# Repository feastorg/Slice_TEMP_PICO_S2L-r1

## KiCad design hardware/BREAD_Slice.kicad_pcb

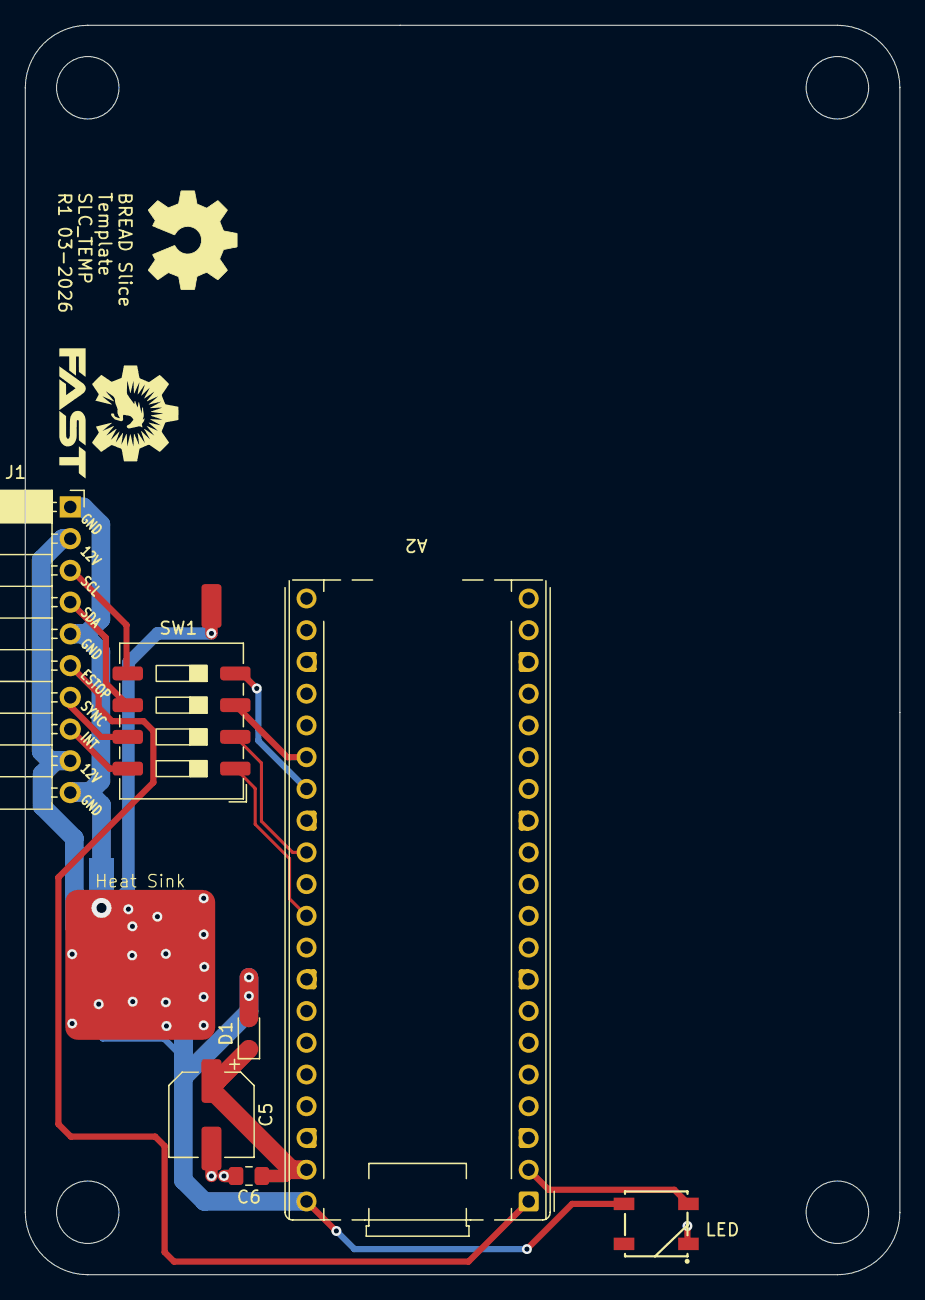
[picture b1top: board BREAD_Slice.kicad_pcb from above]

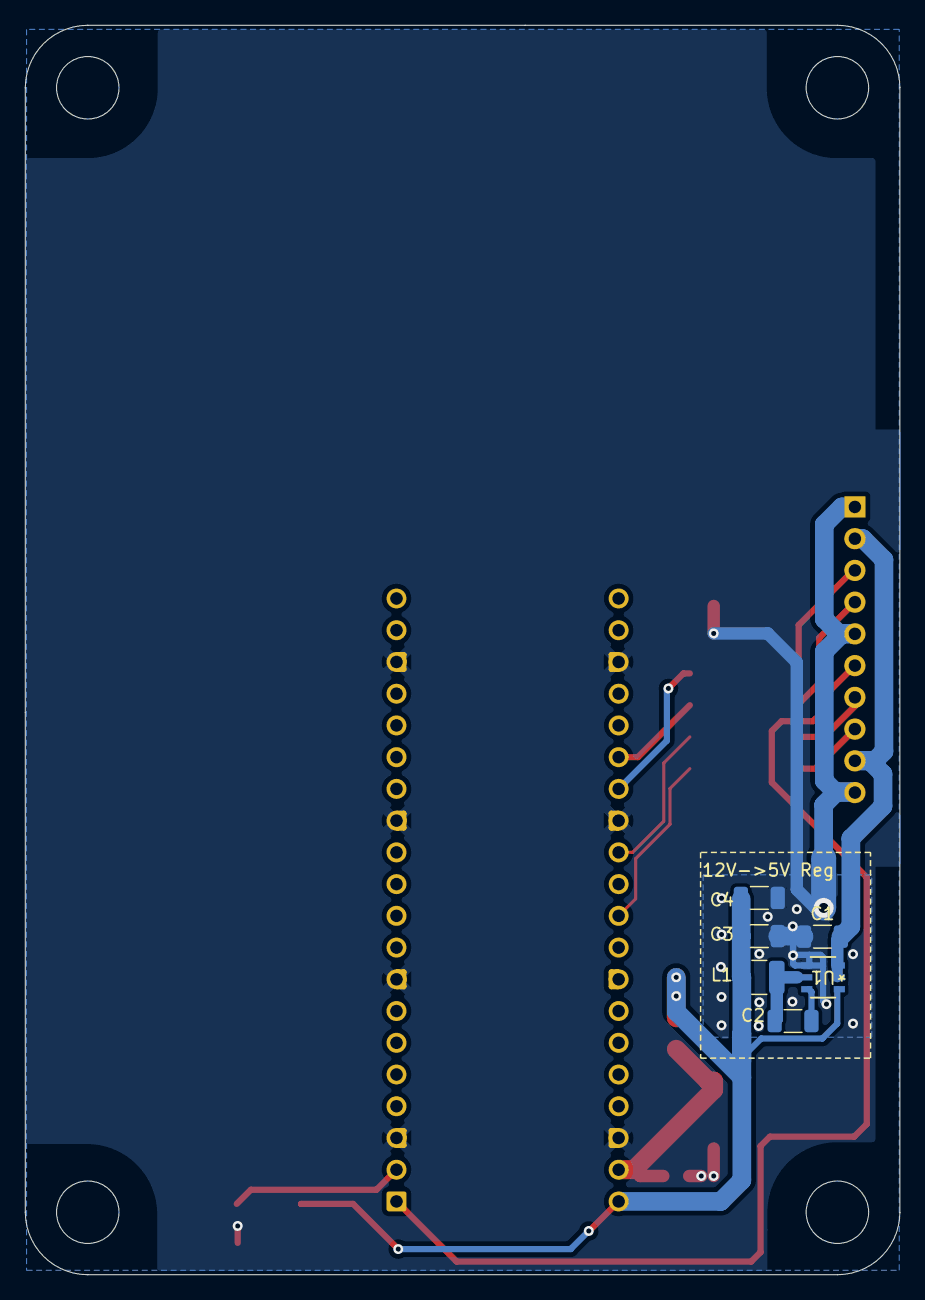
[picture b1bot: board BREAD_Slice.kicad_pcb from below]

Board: 2 copper layers, 70.0 x 100.0 mm, 20 parts (7 on the bottom side), 17 nets.

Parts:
A2: RaspberryPi_Pico; RaspberryPi_Pico_THT
C1: 10u; C_1206_3216Metric
C2: 100nF; C_1206_3216Metric
C3, C4: 22uF; C_1206_3216Metric
C5: 47u 25V; CP_Elec_6.3x7.7
C6: 0.1u; C_0805_2012Metric_Pad1.18x1.45mm_HandSolder
D1: BAT54WS-7-F; D_SOD-323_HandSoldering
D2: WS2812B_5050; WS2812-5050-4PIN
H1, H2, H3, H4: MountingHole; MountingHole_5mm
HS1: Heatsink_Pad; Thermal_Pad
J1: Conn_01x10_Socket; PinSocket_1x10_P2.54mm_Horizontal
L1: 4.7uH; L_1210_3225Metric
NT1: NetTie_2; NetTie-2_SMD_Pad2.0mm
Ref**: Val**; OSHW_Logo_8mm
SW1: SW_DIP_x04; SW_DIP_SPSTx04_Slide_9.78x12.34mm_W8.61mm_P2.54mm
U1: AP63205; SOIC_05WU-7_DIO

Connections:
+5V: A2.40 (VBUS), C3.2, C4.2, D1.2 (A), D2.1 (VDD), L1.2, U1.1 (FB)
+12V: C1.2, J1.2, J1.9, U1.2 (EN), U1.3 (VIN)
/slice_template/ESTOP: A2.1 (GPIO0), J1.6
/slice_template/I2C0_CLK/GPIO21: A2.27 (GPIO21), SW1.4
/slice_template/I2C0_SDA/GPIO20: A2.26 (GPIO20), SW1.3
/slice_template/I2C_CLK: J1.3, SW1.5
/slice_template/I2C_DAT: J1.4, SW1.6
/slice_template/INT: J1.8, SW1.8
/slice_template/INT/CAN_{CS}: A2.31 (GPIO26_ADC0), SW1.1
/slice_template/LED: A2.2 (GPIO1), D2.4 (DIN)
/slice_template/SYNC: J1.7, SW1.7
/slice_template/SYNC/CAN_{INT}: A2.29 (GPIO22), SW1.2
/slice_template/VSYS: A2.39 (VSYS), C5.1, C6.1, D1.1 (K)
GND: A2.3 (GND), A2.8 (GND), A2.13 (GND), A2.18 (GND), A2.23 (GND), A2.28 (GND), A2.38 (GND), C1.1, C3.1, C4.1, C5.2, C6.2, D2.3 (VSS), HS1.1, NT1.1, U1.4 (GND)
GNDPWR: J1.1, J1.5, J1.10, NT1.2
unnamed: C2.2, U1.6 (BST)
unnamed: C2.1, L1.1, U1.5 (SW)

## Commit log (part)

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2026-03-16 Changed to Pico from nano
2026-03-16 changed readme
2026-03-16 added i2c and spi
2026-03-16 add i2c level shifter in todo
2026-03-17 added level shifter and started layout
2026-03-17 finished layout
2026-03-17 added pins 2 and 3 to hierarchical sheet
2026-05-01 chore: untrack macos system files
2026-05-01 chore: untrack schematic backups
2026-05-01 pcb: minor changes and silk screen version
2026-05-01 chore: change version to v1 to align with template name
2026-05-01 fix: rewire gnd caps around pico
2026-05-01 📄 KiBot index + board renders (auto)
2026-05-20 Add slice.yaml manifest (schema v1.0)
2026-05-24 Add standardized TODO.md with Pass 1/Pass 2 structure
